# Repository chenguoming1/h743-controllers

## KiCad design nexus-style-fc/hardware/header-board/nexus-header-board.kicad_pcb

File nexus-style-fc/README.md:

# Nexus-style FBL controller

Latest assembly sourcing update: [R23 replacement, 18 October 2026](docs/validation/reviews/r23-replacement-2026-10-18/REVIEW.md). R23 is C2766886 / Uniroyal 0402WGJ012KTCE, 0.12 Ω ±5%. Only component metadata and BOM change; Gerbers, routing and CPL remain unchanged.

A KiCad 10 F722 controller based on the RadioMaster Nexus form factor and Rotorflight RDMS-NEXUS_F7 resource map. Orientation, bring-up and physical qualification remain unverified.

**Two-board prototype package prepared. Factory process review and physical bring-up remain required before relying on this design; flight qualification is unverified.**

## Open the current design

- [Main KiCad project](hardware/nexus-style-fc.kicad_pro), [main PCB](hardware/nexus-style-fc.kicad_pcb), [main schematic](hardware/nexus-style-fc.kicad_sch)
- [Servo-header child project](hardware/header-board/nexus-header-board.kicad_pro), [child PCB](hardware/header-board/nexus-header-board.kicad_pcb), [child schematic](hardware/header-board/nexus-header-board.kicad_sch)
- [Current prototype Gerber, BOM and CPL files](manufacturing/README.md)
- [Validation, exact source provenance and open gates](docs/validation/README.md)

There is one working design in this project root. `hardware/`, `tools/` and `manufacturing/` hold the current trace-corrected main and four-layer power-upgraded child. Work directly here on a Git branch; use commits, branches and pull requests for revisions. Older project snapshots are available in Git history, rather than additional working version folders. The other repository projects are unchanged.

## Source layout

| Path | Purpose |
| --- | --- |
| `hardware/` | Authoritative routed main board, schematic, project settings and rules |
| `hardware/header-board/` | Matching child board and its separate KiCad project |
| `hardware/library/` | Shared local symbols, footprints and 3D models |
| `tools/` | Part/placement definitions, legacy generators, routing helpers and read-only validation |
| `manufacturing/` | Matching prototype order exports and explicit factory requirements |
| `firmware/RDMS-NEXUS_F7.config` | Unchanged upstream resource-map reference |
| `docs/validation/` | Current validation plus revision-labelled historical evidence |

## Validate safely

Install KiCad 10 with its standard symbols, footprints and models. The project's relative local-library and model paths work from these canonical locations. Native Python helpers need the Python interpreter bundled with KiCad, or one with its matching `pcbnew` module. On Linux, the standard libraries are normally under `/usr/share/kicad`; `KICAD_SYMBOL_DIR`, `KICAD_FOOTPRINT_DIR` or `KICAD10_FOOTPRINT_DIR` can override the corresponding lookup.

From this directory:

```sh
KICAD_CLI=kicad-cli KICAD_PYTHON=python3 bash tools/validate_project.sh
```

This checks paths, Python syntax, ERC and DRC with schematic parity and writes reports to a temporary directory. It does not refill zones or save either board. Native KiCad may create ignored `.kicad_prl` UI-state files. Pass an output-directory argument to retain reports elsewhere. Review all warnings and inherited exclusions; a zero-error result is not physical or manufacturing approval.

**Do not run `build_all.sh` to validate or reproduce the routed boards.** The legacy generator overwrites footprints, schematics and boards with a new baseline; it does not reproduce the accepted manual routing or the complete child integration. Its default invocation now refuses to overwrite anything. The explicit `--regenerate-unrouted` option is only for intentional experiments in a disposable Git worktree. Direct generator/routing scripts can also overwrite files. `design.py` is the current part/placement definition, while the checked-in native boards remain authoritative for routed copper and fills.

## Current evidence and remaining gates

Latest source/CAM binding and checks: [standard-stack adaptation](docs/validation/reviews/standard-stack-2026-10-17/REVIEW.md). Main uses standard JLC06161H-3313 with In1/In2 copper content exchanged and a 0.132/0.165 mm L4 USB trunk. Components, vias, outline, VCAP and power-track widths are preserved.

The [order-fixes review](docs/validation/reviews/order-fixes-2026-10-17/REVIEW.md) documents the preceding electrical/mechanical fixes for **two assembled main prototypes plus matching child PCBs**. It includes C9/R23 VCAP damping, a 7.4 V BEC-appropriate TVS, improved mating clearance, 0.26 mm child header rings and round USB shell holes. Native main ERC/DRC/opens/parity are all zero. Child ERC/errors/opens/parity are zero with 11 bare-contact courtyard warnings. Fresh main BOM/CPL has 53 groups / 84 placements, all groups matched in JLCDFM; both current Gerber ZIPs were freshly analyzed.

The owner's 5V_BUCK widening and USB centerlines are preserved. Main requires the [six-layer standard JLC06161H-3313 stack and nominal 90 Ω USB routing](manufacturing/nexus-style-fc/FABRICATION-NOTES.md), and filled/capped POFV for **all 228 main vias**. Child requires its separate [four-layer JLC041622-3313, 2 oz outer AND inner settings](manufacturing/nexus-header-board/FABRICATION-NOTES.md). Current-source child copper-loss calculation is about 0.275 W at the imposed 19.6 A dual-feed stress condition; it is not a thermal or connector/BEC rating. Retained contacts are 3 A each.

Use [ORDER-INSTRUCTIONS.txt](manufacturing/ORDER-INSTRUCTIONS.txt) for the exact files/settings. Factory acceptance of stack/impedance, POFV, paired-board fit, short USB shell-leg soldering and dense placement remains necessary. The full VCAP/USB/electrical, transient, mechanical, firmware and flight behavior needs prototype testing. Historical reports remain evidence of their named revisions and do not bind the new exports.

## Attribution and sibling project

The [Rotorflight target reference](firmware/RDMS-NEXUS_F7.config) is copied unchanged from [rotorflight-targets](https://github.com/rotorflight/rotorflight-targets/blob/b89676f/configs/RDMS-NEXUS_F7.config), recorded upstream revision `b89676f` (2026-03-02), and remains attributed to its authors. No firmware binary is included. RadioMaster branding is not used on the board.

The separate [power module](../nexus-style-fc-power-module/) uses the shared legacy `PARTS` interface; the current main-board selection is isolated in `get_main_parts()`.

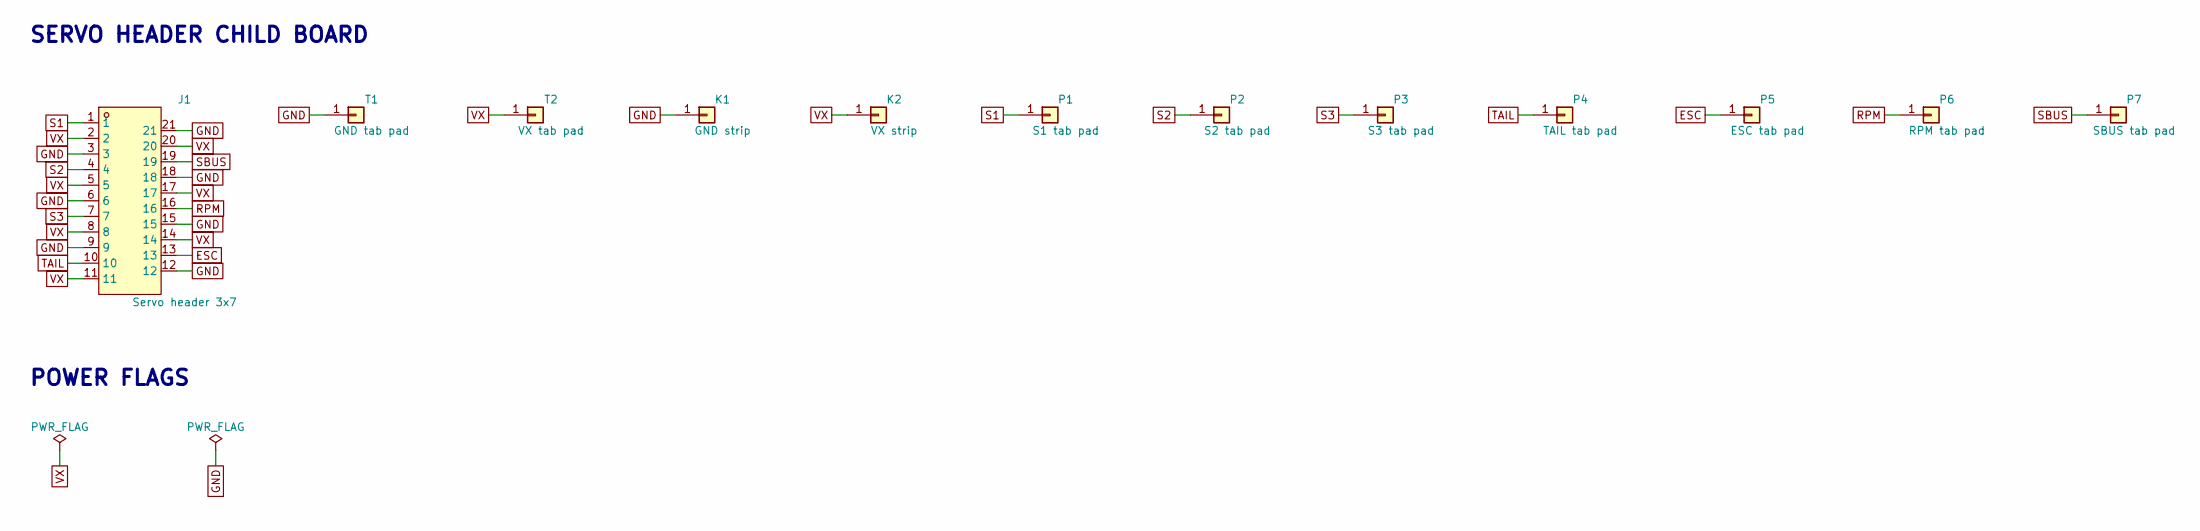
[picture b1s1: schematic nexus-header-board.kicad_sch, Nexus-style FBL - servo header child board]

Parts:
J1: Servo header 3x7; Header_3x07_P2.54_Vertical_Servo; LCSC C32713294
K1: GND strip; ChildBoard_TabStrip_W7.892
K2: VX strip; ChildBoard_TabStrip_W7.892
P1: S1 tab pad; ChildBoard_TabPad_Sig
P2: S2 tab pad; ChildBoard_TabPad_Sig
P3: S3 tab pad; ChildBoard_TabPad_Sig
P4: TAIL tab pad; ChildBoard_TabPad_Sig
P5: ESC tab pad; ChildBoard_TabPad_Sig
P6: RPM tab pad; ChildBoard_TabPad_Sig
P7: SBUS tab pad; ChildBoard_TabPad_Sig
T1: GND tab pad; ChildBoard_TabPad_Pwr
T2: VX tab pad; ChildBoard_TabPad_Pwr

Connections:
ESC: J1.13, P5.1
GND: J1.3, J1.6, J1.9, J1.12, J1.15, J1.18, J1.21, K1.1, T1.1
RPM: J1.16, P6.1
S1: J1.1, P1.1
S2: J1.4, P2.1
S3: J1.7, P3.1
SBUS: J1.19, P7.1
TAIL: J1.10, P4.1
VX: J1.2, J1.5, J1.8, J1.11, J1.14, J1.17, J1.20, K2.1, T2.1

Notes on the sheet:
SERVO HEADER CHILD BOARD
POWER FLAGS

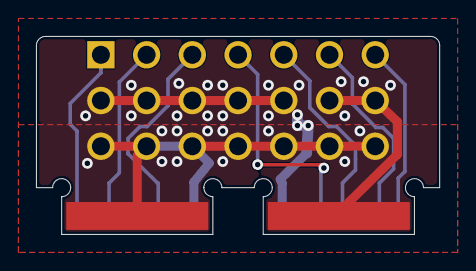
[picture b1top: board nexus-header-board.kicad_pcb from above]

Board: 4 copper layers, 22.4 x 11.0 mm, 12 parts (0 on the bottom side), 9 nets.

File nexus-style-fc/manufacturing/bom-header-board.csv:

"Designator","Value","Footprint","LCSC Part #","Quantity"
"J1","Servo header 3x7","NexusFC:Header_3x07_P2.54_Vertical_Servo","C32713294","1"
"K1,K3","GND strip","NexusFC:ChildBoard_TabStrip_W6.0","","2"
"K2","VX strip","NexusFC:ChildBoard_TabStrip_W6.2","","1"
"P1","S1 tab pad","NexusFC:ChildBoard_TabPad_Sig","","1"
"P2","S2 tab pad","NexusFC:ChildBoard_TabPad_Sig","","1"
"P3","S3 tab pad","NexusFC:ChildBoard_TabPad_Sig","","1"
"P4","TAIL tab pad","NexusFC:ChildBoard_TabPad_Sig","","1"
"P5","ESC tab pad","NexusFC:ChildBoard_TabPad_Sig","","1"
"P6","RPM tab pad","NexusFC:ChildBoard_TabPad_Sig","","1"
"P7","SBUS tab pad","NexusFC:ChildBoard_TabPad_Sig","","1"
"T1","GND tab pad","NexusFC:ChildBoard_TabPad_Pwr","","1"
"T2","VX tab pad","NexusFC:ChildBoard_TabPad_Pwr","","1"
